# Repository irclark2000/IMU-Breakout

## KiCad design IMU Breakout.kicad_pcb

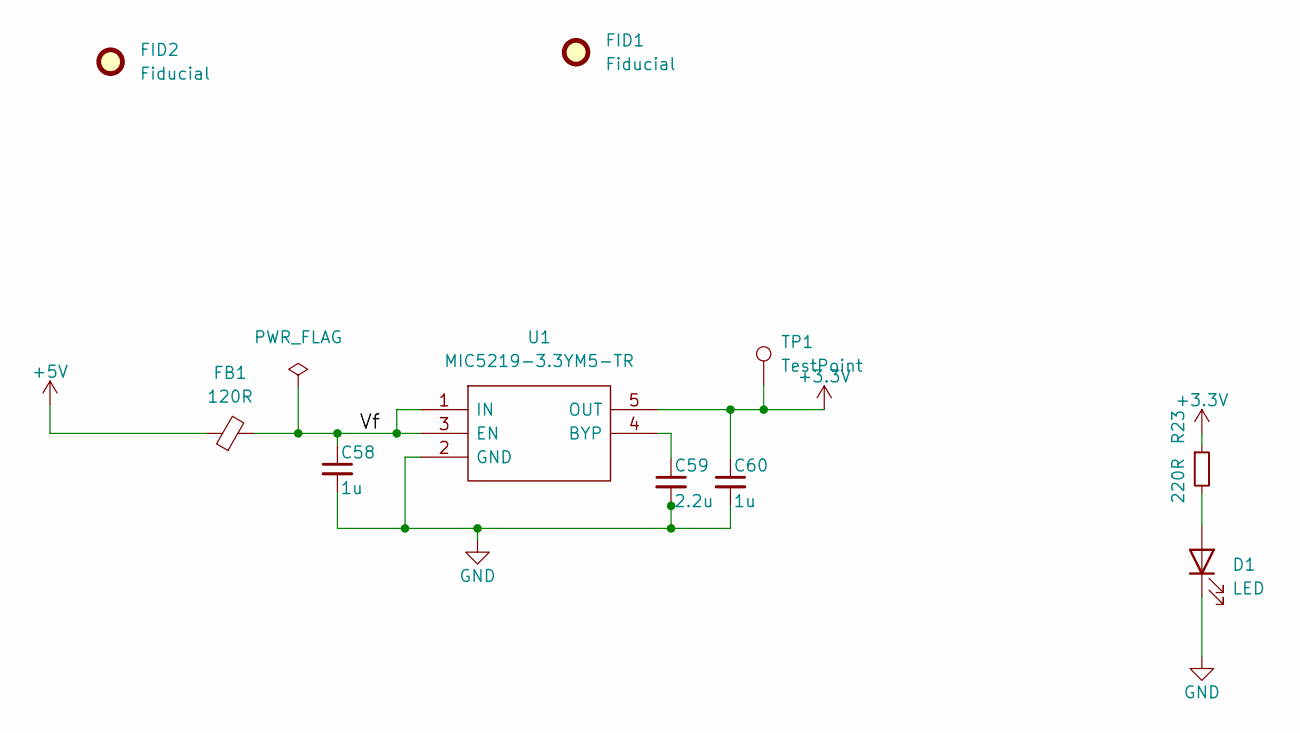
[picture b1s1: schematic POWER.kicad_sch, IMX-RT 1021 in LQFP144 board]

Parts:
C58, C60: 1u; C_0402_1005Metric
C59: 2.2u; C_0402_1005Metric
D1: LED; LED_0402_1005Metric
FB1: 120R; BLM18AG102BH1D
FID1, FID2: Fiducial; Fiducial_0.75mm_Mask1.5mm
R23: 220R; R_0402_1005Metric
TP1: TestPoint; TestPoint_Pad_D1.0mm
U1: MIC5219-3.3YM5-TR; SOT95P280X145-5N; Manufacturer_Part_Number MIC5219-3.3YM5-TR; Mouser Part Number 998-MIC5219-3.3YM5TR

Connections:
+3V3: C60.1, R23.1, TP1.1, U1.5 (OUT); also elsewhere on the board
+5V: FB1.1; also elsewhere on the board
/POWER/Vf: C58.1, FB1.2, U1.1 (IN), U1.3 (EN)
GND: C58.2, C59.2, C60.2, D1.1 (K), U1.2 (GND); also elsewhere on the board
unnamed: C59.1, U1.4 (BYP)
unnamed: D1.2 (A), R23.2

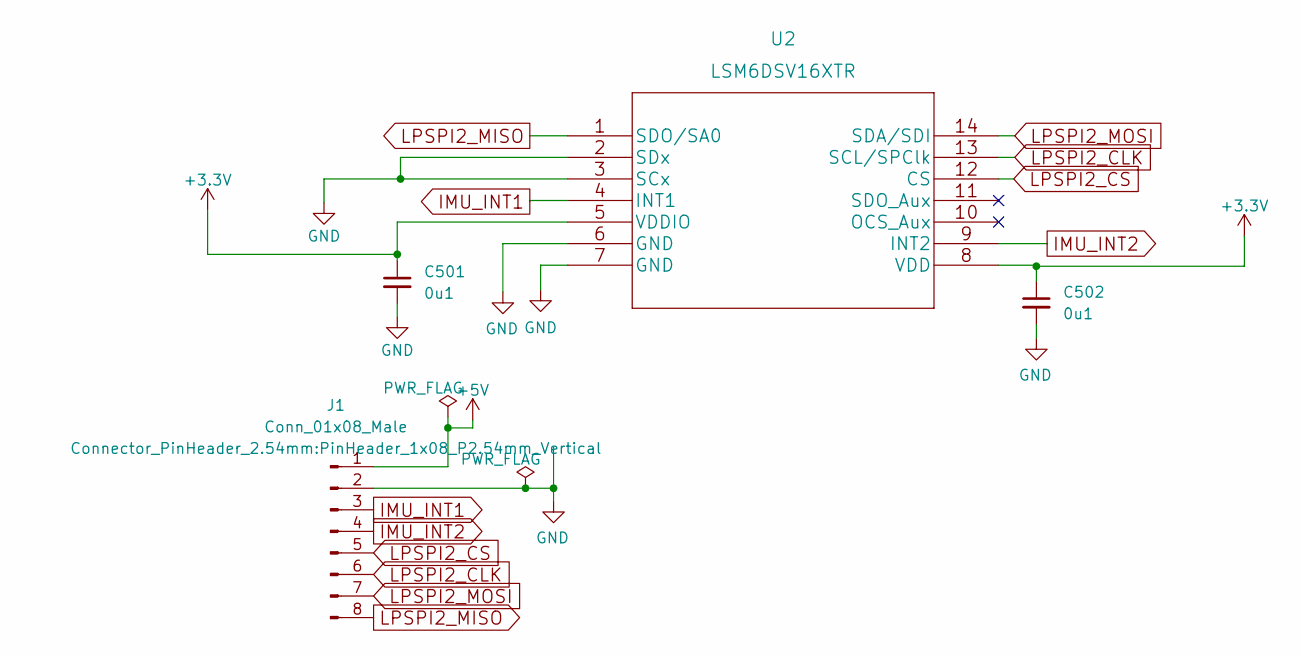
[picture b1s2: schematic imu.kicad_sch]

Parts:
C501, C502: 0u1; C_0402_1005Metric
J1: Conn_01x08_Male; PinHeader_1x08_P2.54mm_Vertical
U2: LSM6DSV16XTR; LGA-14_1

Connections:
+3V3: C501.1, C502.1, U2.5 (VDDIO), U2.8 (VDD); also elsewhere on the board
+5V: J1.1; also elsewhere on the board
GND: C501.2, C502.2, J1.2, U2.2 (SDx), U2.3 (SCx), U2.6 (GND), U2.7 (GND); also elsewhere on the board
IMU_INT1: J1.3, U2.4 (INT1)
IMU_INT2: J1.4, U2.9 (INT2)
LPSPI2_CLK: J1.6, U2.13 (SCL/SPClk)
LPSPI2_CS: J1.5, U2.12 (CS)
LPSPI2_MISO: J1.8, U2.1 (SDO/SA0)
LPSPI2_MOSI: J1.7, U2.14 (SDA/SDI)

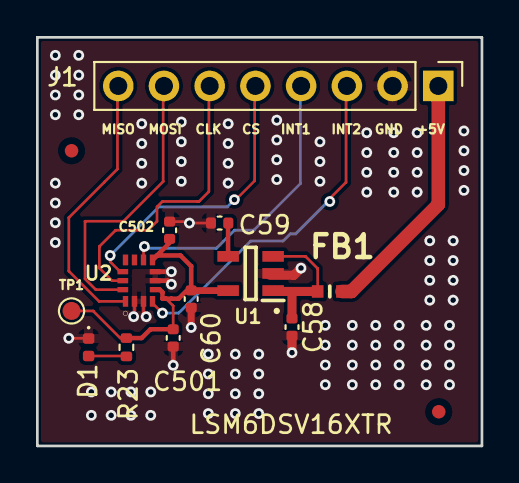
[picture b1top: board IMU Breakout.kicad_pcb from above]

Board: 2 copper layers, 24.7 x 22.7 mm, 14 parts (0 on the bottom side), 12 nets.

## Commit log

2023-02-02 Initial commit
    Initial layout
2023-02-02 Readme replacement
